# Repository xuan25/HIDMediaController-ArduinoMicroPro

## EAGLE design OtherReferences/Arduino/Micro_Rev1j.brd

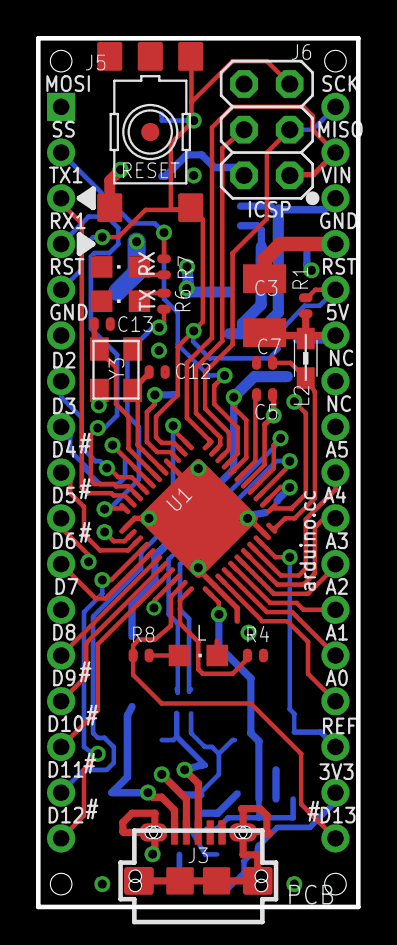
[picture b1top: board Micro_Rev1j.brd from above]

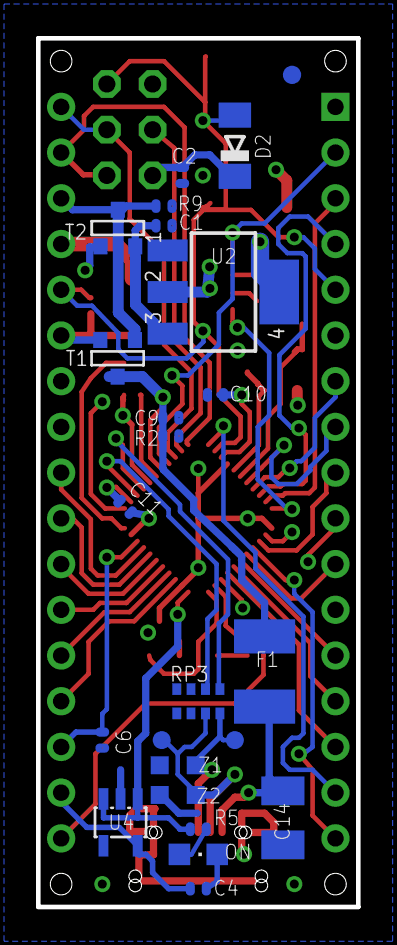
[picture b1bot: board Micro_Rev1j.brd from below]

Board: 4 copper layers, 17.8 x 48.3 mm, 47 parts (22 on the bottom side), 47 nets.

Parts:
C1, C2, C6, C9, C10, C11: 100n; C0402
C3, C14: 22u; SMC_B
C4, C5, C7: 1uF; C0402
C12, C13: 22pF; C0402
D2: CD1206-S01575; MINIMELF
D+: DNP; TP-1.00MM
D-: DNP; TP-1.00MM
F1: MF-MSMF050-2 500mA; L1812
FRAME1: DNP; FRAME
J3: USB-MICRO!!!; CON2_USB_MICRO_B_AT
J4: 3x2M; 2X03
J5: HEAD17-NOSS
J6: HEAD17-NOSS-1
L: green; CHIPLED_0805
L2: MH2029-300Y; 0805
ON: blue; CHIPLED_0805
R1, R2, R4, R9: 10K; R0402
R5, R6, R7, R8: 1K; R0402
RESET: TS42
RP3: 22R; CAY16
RX: yellow; CHIPLED_0805
T1: FDN340P/PMV48XP; SOT-23
T2: PMV48XP; SOT-23
TX: yellow; CHIPLED_0805
U1: ATMEGA32U4-XUMU; QFN44ML7X7
U2: NCP1117-5; SOT223
U4: LP2985-33DBVR; SOT23-DBV
U$37, U$53: DNP; FD-1-1.5
Y3: 16MHz KX-7; CRYSTAL-3.2-2.5
Z1, Z2: CG0603MLC-05E; CT/CN0603

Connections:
3V3: C4.1, J6.16, U4.5
+5V: C2.1, C3.+, C10.1, C11.1, D2.C, J4.2, J6.6, L2.1, R1.1, R5.1, T1.2, T2.3, U1.2, U1.14, U1.24, U1.34, U2.2, U2.4, U4.1, U4.3
+VIN: C1.1, T2.2, U2.3
A0: J6.14, U1.36
A1: J6.13, U1.37
A2: J6.12, U1.38
A3: J6.11, U1.39
A4: J6.10, U1.40
A5: J6.9, U1.41
AREF: C6.1, J6.15, U1.42
AVCC: C7.1, L2.2, U1.44
D0/RX: J5.4, U1.20
D1/TX: J5.3, U1.21
D2/SDA: J5.7, U1.19
D3/SCL: J5.8, U1.18
D4*: J5.9, U1.25
D5*: J5.10, U1.31
D6*: J5.11, U1.27
D7: J5.12, U1.1
D+: D+.X, J3.P3, RP3.8, Z1.1
D-: D-.X, J3.P2, RP3.7, Z2.1
GND: C1.2, C2.2, C3.-, C4.2, C5.2, C6.2, C7.2, C9.2, C10.2, C11.2, C12.1, C13.1, C14.-, J3.P5, J3.S1, J3.S2, J3.S3, J3.S4, J3.S5, J3.S6, J4.6, J5.6, J6.4, L.C, ON.C, R2.1, R4.2, R9.1, RESET.3, RESET.4, RESET.5, RP3.3, RP3.4, RP3.5, RP3.6, RX.C, TX.C, U1.5, U1.15, U1.23, U1.35, U1.43, U1.EXP, U2.1, U4.2, Y3.2, Y3.4, Z1.2, Z2.2
HWB: R4.1, U1.33
IO8: J5.13, U1.28
IO9*: J5.14, U1.29
IO10*: J5.15, U1.30
IO11*: J5.16, U1.12
IO12*: J5.17, U1.26
IO13*: J6.17, R8.1, U1.32
MISO: J4.1, J6.2, U1.11
MOSI: J4.4, J5.1, U1.10
unnamed: R7.2, RX.A
unnamed: ON.A, R5.2
unnamed: R6.2, TX.A
unnamed: L.A, R8.2
RD+: RP3.1, U1.4
RD-: RP3.2, U1.3
RESET: D2.A, J4.5, J5.5, J6.5, R1.2, RESET.1, RESET.2, U1.13
RXLED/SS: J5.2, R7.1, U1.8
SCK: J4.3, J6.1, U1.9
TXLED: R6.1, U1.22
UCAP: C5.1, U1.6
VIN: J6.3, R9.2, T1.3, T2.1
VUSB: C9.1, F1.2, R2.2, T1.1, U1.7
VUSBD: C14.+, F1.1, J3.P1
XTAL1: C13.2, U1.17, Y3.3
XTAL2: C12.2, U1.16, Y3.1

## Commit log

2018-10-21 Upload module
2018-10-21 Update Packages/boards/MediaController.txt
    Modified board info
2018-10-21 Update Upload/supports/MediaController.hex
    Change device name
2018-10-21 Change ino name
2018-10-21 Define keys
2018-10-21 New code structrue
2018-10-21 PS ControllerDemo
2018-10-22 Add comments
2018-10-22 Change structure
2018-10-22 Update Code/MediaController_PSdemo/MediaController_PSdemo.ino
    Increase delay
2018-10-26 Fix the issue on volume control
2021-01-03 Code cleanup

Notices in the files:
OtherReferences/Arduino/Micro_Rev1j.brd:
Copyright (c) 2016-2017 Arduino LLC.  All right reserved. EAGLE Design Rules
parts and their libraries:
Arduino-utility: Copyright (c) 2016-2017 Arduino LLC.  All right reserved.
